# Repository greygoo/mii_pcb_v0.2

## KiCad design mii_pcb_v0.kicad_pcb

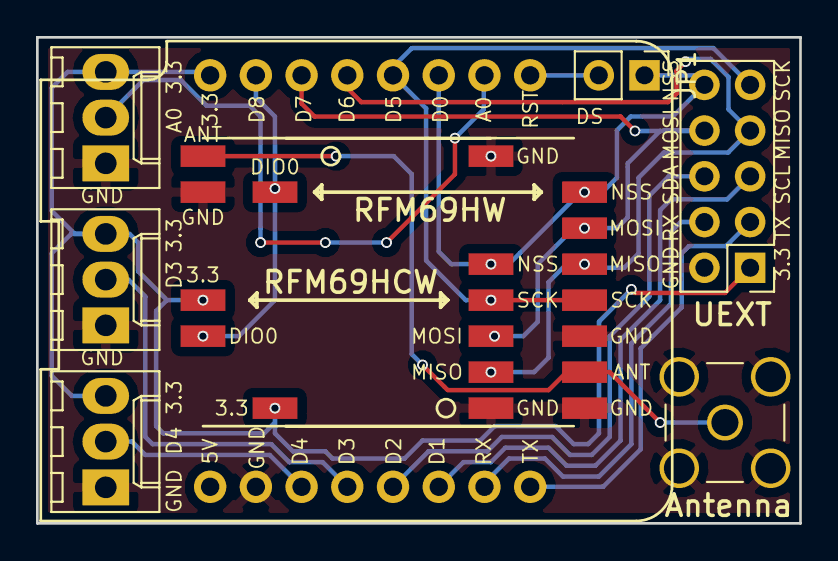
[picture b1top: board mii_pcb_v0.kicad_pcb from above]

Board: 2 copper layers, 42.4 x 27.0 mm, 9 parts (0 on the bottom side), 16 nets.

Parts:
J1: CONN_02X05; Pin_Header_Straight_2x05_Pitch2.54mm
J2: CONN_COAXIAL; SMA_THT_Jack_Straight
J3, J4, J5: CONN_01X03; Molex_KK-6410-03_03x2.54mm_Straight
JP1: Jumper; Pin_Header_Straight_1x02_Pitch2.54mm
U1: WeMos_mini; wemos-d1-mini-connectors-only
U2: RFM69HW; RFM69
U3: RFM69HCW

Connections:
/3.3V: J1.1, J3.3, J4.3, J5.3, U1.16, U2.8, U3.13
/A0: J3.2, U1.10
/ANT: J2.1, U2.10, U3.9
/BTN: J5.2, U1.3
/FLASH: J4.2, U1.4
/GND: J1.2, J2.2, J3.1, J4.1, J5.1, U1.2, U2.9, U2.11, U3.1, U3.8, U3.10
/IRQ: U1.15, U2.2, U3.14
/MISO: J1.7, U1.13, U2.13, U3.2
/MOSI: J1.8, U1.14, U2.14, U3.3
/NSS: J1.10, JP1.1, U1.11, U2.15, U3.5
/RST: JP1.2, U1.9
/RX: J1.4, U1.7
/SCK: J1.9, U1.12, U2.12, U3.4
/SCL: J1.5, U1.6
/SDA: J1.6, U1.5
/TX: J1.3, U1.8

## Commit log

2018-11-05 Add required git submodules
2018-11-05 Add kicad files
2018-11-06 new pcb
2018-11-06 Add local libs to project
2018-11-26 Add jumper for Deepsleep
